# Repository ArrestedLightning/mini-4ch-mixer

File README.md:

# Mini 4 Channel Audio Mixer

A very simple active audio mixer with 4 3.5mm inputs, and 1 3.5mm output.  USB-powered.  The default gain is 1:1 on all channels, although this can be changed by altering resistor values and/or installing potentiometers.  I built this as a simple way to run multiple sources into a set of computer speakers.  It is designed to fit in a commonly-available 90x70x28mm enclosure with end panels that can be either laser-cut or made from PCBs.

This project uses symbols from https://github.com/ArrestedLightning/al_kicad_libraries/.  It is licensed CC BY 4.0.

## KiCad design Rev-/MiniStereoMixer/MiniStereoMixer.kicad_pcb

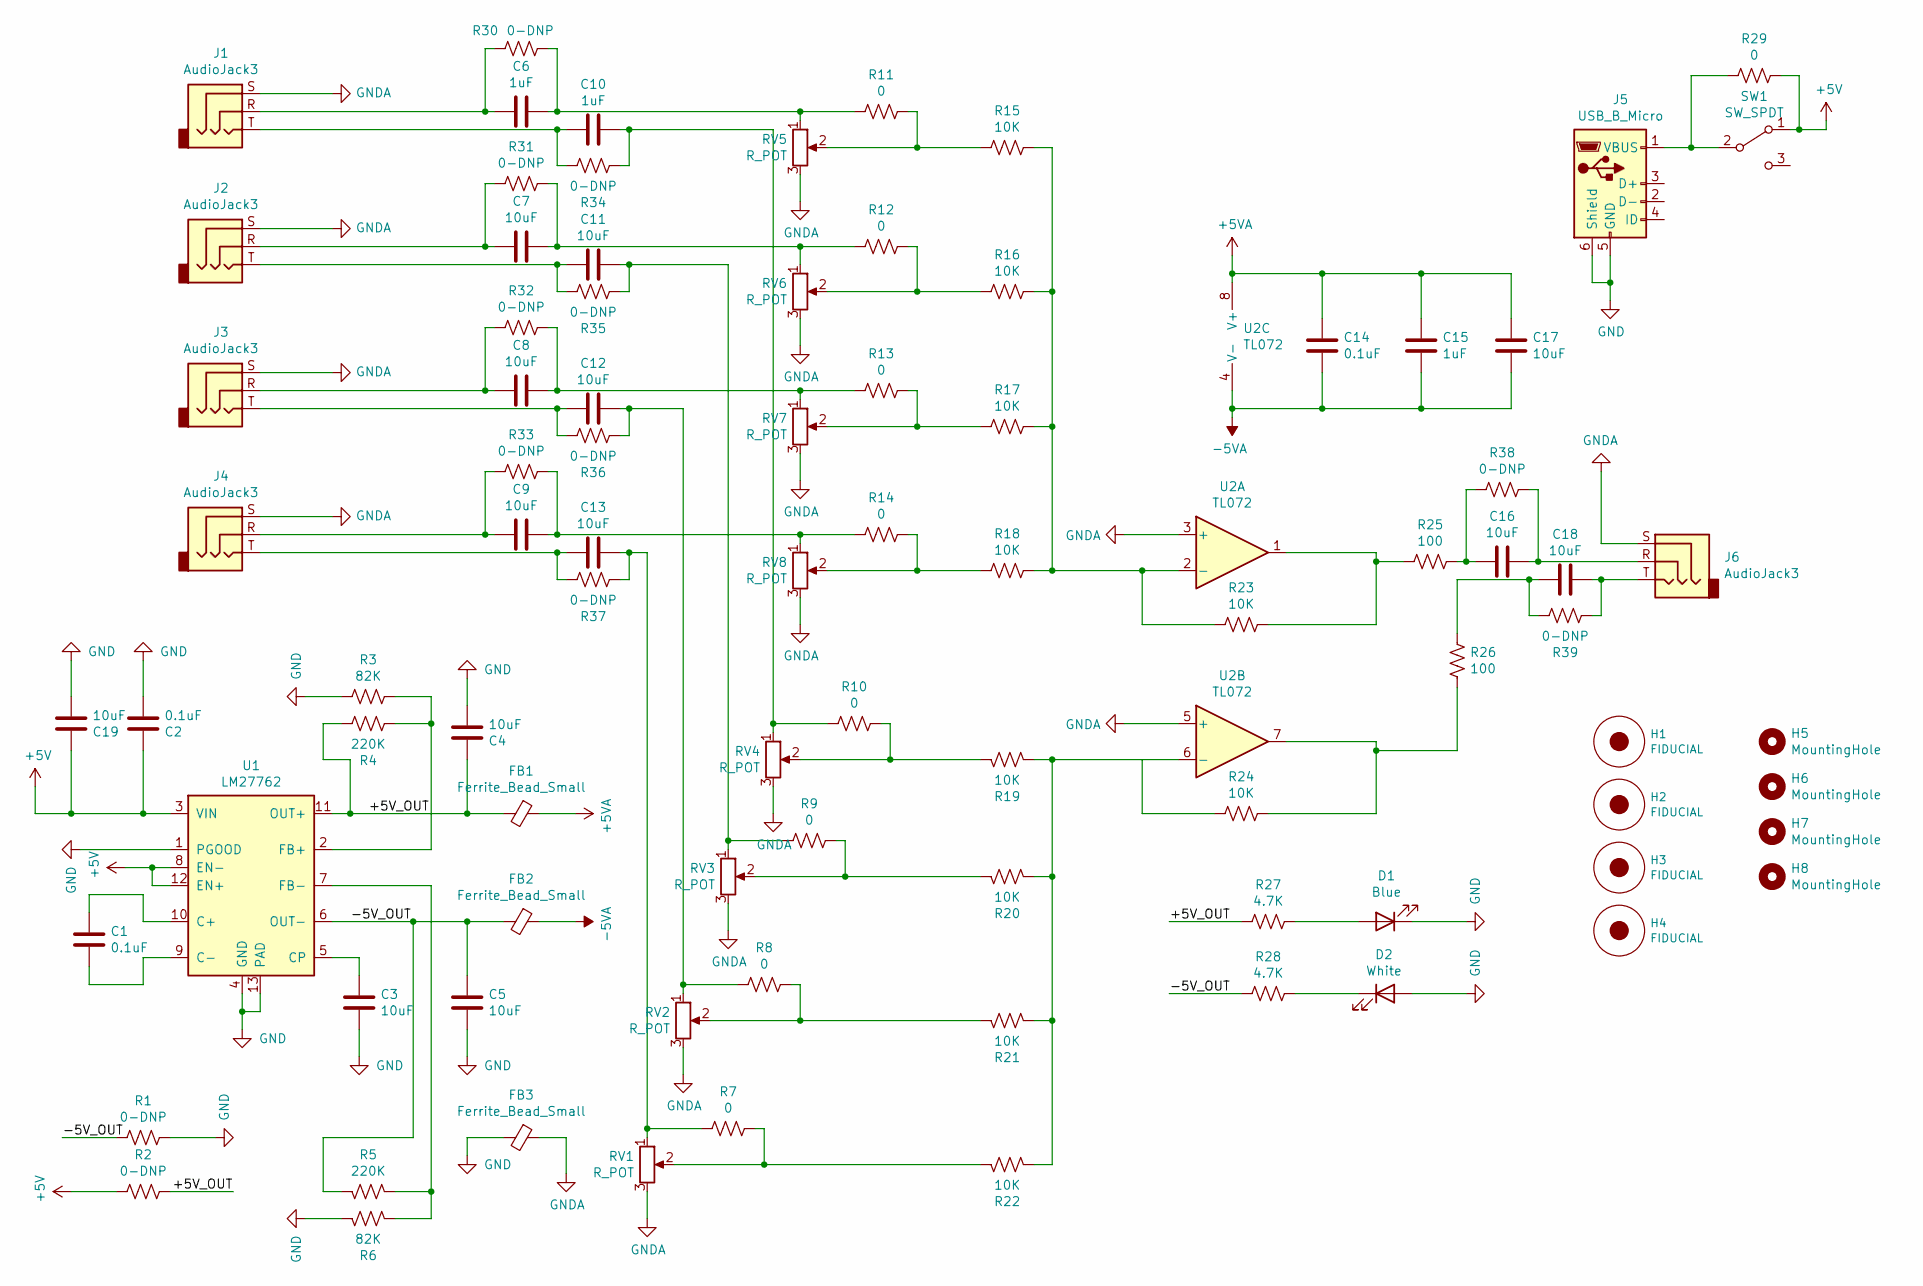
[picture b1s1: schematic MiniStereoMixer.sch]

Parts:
C1, C2, C14: 0.1uF; C_0805_2012Metric_Pad1.15x1.40mm_HandSolder; JLCPCB C49678
C3, C4, C5, C7, C8, C9, C11, C12, C13, C16, C17, C18, C19: 10uF; C_0805_2012Metric_Pad1.15x1.40mm_HandSolder; JLCPCB C15850
C6, C10, C15: 1uF; C_0805_2012Metric_Pad1.15x1.40mm_HandSolder; JLCPCB C28323
D1: Blue; LED_0805_2012Metric_Pad1.15x1.40mm_HandSolder; JLCPCB C2293
D2: White; LED_0805_2012Metric_Pad1.15x1.40mm_HandSolder; JLCPCB C34499
FB1, FB2, FB3: Ferrite_Bead_Small; R_0805_2012Metric_Pad1.15x1.40mm_HandSolder; JLCPCB C1017
H1, H2, H3, H4: FIDUCIAL; Fiducial_1.5mm_Mask3mm
H5, H6, H7, H8: MountingHole; MountingHole_3.2mm_M3_Pad
J1, J2, J3, J4, J6: AudioJack3; 3.5mmAudioJack
J5: USB_B_Micro; USB_Micro_A_SMD_HANDSOLDER_SMALLPADS
R1, R2, R30, R31, R32, R33, R34, R35, R36, R37, R38, R39: 0-DNP; R_0805_2012Metric_Pad1.15x1.40mm_HandSolder
R3, R6: 82K; R_0805_2012Metric_Pad1.15x1.40mm_HandSolder; JLCPCB C17840
R4, R5: 220K; R_0805_2012Metric_Pad1.15x1.40mm_HandSolder; JLCPCB C17556
R7, R8, R9, R10, R11, R12, R13, R14, R29: 0; R_0805_2012Metric_Pad1.15x1.40mm_HandSolder; JLCPCB C17477
R15, R16, R17, R18, R19, R20, R21, R22, R23, R24: 10K; R_0805_2012Metric_Pad1.15x1.40mm_HandSolder; JLCPCB C17414
R25, R26: 100; R_0805_2012Metric_Pad1.15x1.40mm_HandSolder; JLCPCB C17408
R27, R28: 4.7K; R_0805_2012Metric_Pad1.15x1.40mm_HandSolder; JLCPCB C17673
RV1, RV2, RV3, RV4, RV5, RV6, RV7, RV8: R_POT; potentiometer_3x5mm
SW1: SW_SPDT; PinHeader_1x03_P2.54mm_Horizontal
U1: LM27762; WSON-12-1EP_3x2mm_P0.5mm_EP1x2.65_ThermalVias; JLCPCB C134018
U2: TL072; SO-8_3.9x4.9mm_P1.27mm; JLCPCB C6961

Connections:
+5V: C2.1, C19.1, R2.2, R29.1, SW1.1 (A), U1.3 (VIN), U1.8 (EN-), U1.12 (EN+)
+5VA: C14.1, C15.1, C17.1, FB1.1, U2.8 (V+)
-5VA: C14.2, C15.2, C17.2, FB2.1, U2.4 (V-)
/+5V_OUT: C4.1, FB1.2, R2.1, R4.1, R27.2, U1.11 (OUT+)
/-5V_OUT: C5.1, FB2.2, R1.2, R5.1, R28.2, U1.6 (OUT-)
GND: C2.2, C3.2, C4.2, C5.2, C19.2, D1.1 (K), D2.2 (A), FB3.2, J5.5 (GND), J5.6 (Shield), R1.1, R3.2, R6.2, U1.1 (PGOOD), U1.4 (GND), U1.13 (PAD)
GNDA: FB3.1, J1.S, J2.S, J3.S, J4.S, J6.S, RV1.3, RV2.3, RV3.3, RV4.3, RV5.3, RV6.3, RV7.3, RV8.3, U2.3 (+), U2.5 (+)
unnamed: C1.1, U1.10 (C+)
unnamed: C1.2, U1.9 (C-)
unnamed: C3.1, U1.5 (CP)
unnamed: C6.1, R11.2, R30.1, RV5.1
unnamed: C6.2, J1.R, R30.2
unnamed: C7.1, R12.2, R31.1, RV6.1
unnamed: C7.2, J2.R, R31.2
unnamed: C8.1, R13.2, R32.1, RV7.1
unnamed: C8.2, J3.R, R32.2
unnamed: C9.1, R14.2, R33.1, RV8.1
unnamed: C9.2, J4.R, R33.2
unnamed: C10.1, R10.2, R34.2, RV4.1
unnamed: C10.2, J1.T, R34.1
unnamed: C11.1, R9.2, R35.2, RV3.1
unnamed: C11.2, J2.T, R35.1
unnamed: C12.1, R8.2, R36.2, RV2.1
unnamed: C12.2, J3.T, R36.1
unnamed: C13.1, R7.2, R37.2, RV1.1
unnamed: C13.2, J4.T, R37.1
unnamed: C16.1, J6.R, R38.1
unnamed: C16.2, R25.1, R38.2
unnamed: C18.1, J6.T, R39.2
unnamed: C18.2, R26.2, R39.1
unnamed: D1.2 (A), R27.1
unnamed: D2.1 (K), R28.1
unnamed: J5.1 (VBUS), R29.2, SW1.2 (B)
unnamed: R3.1, R4.2, U1.2 (FB+)
unnamed: R5.2, R6.1, U1.7 (FB-)
unnamed: R10.1, R19.2, RV4.2
unnamed: R11.1, R15.2, RV5.2
unnamed: R12.1, R16.2, RV6.2
unnamed: R13.1, R17.2, RV7.2
unnamed: R14.1, R18.2, RV8.2
unnamed: R15.1, R16.1, R17.1, R18.1, R23.2, U2.2 (-)
unnamed: R19.1, R20.1, R21.1, R22.1, R24.2, U2.6 (-)
unnamed: R9.1, R20.2, RV3.2
unnamed: R8.1, R21.2, RV2.2
unnamed: R7.1, R22.2, RV1.2
unnamed: R23.1, R25.2, U2.1
unnamed: R24.1, R26.1, U2.7

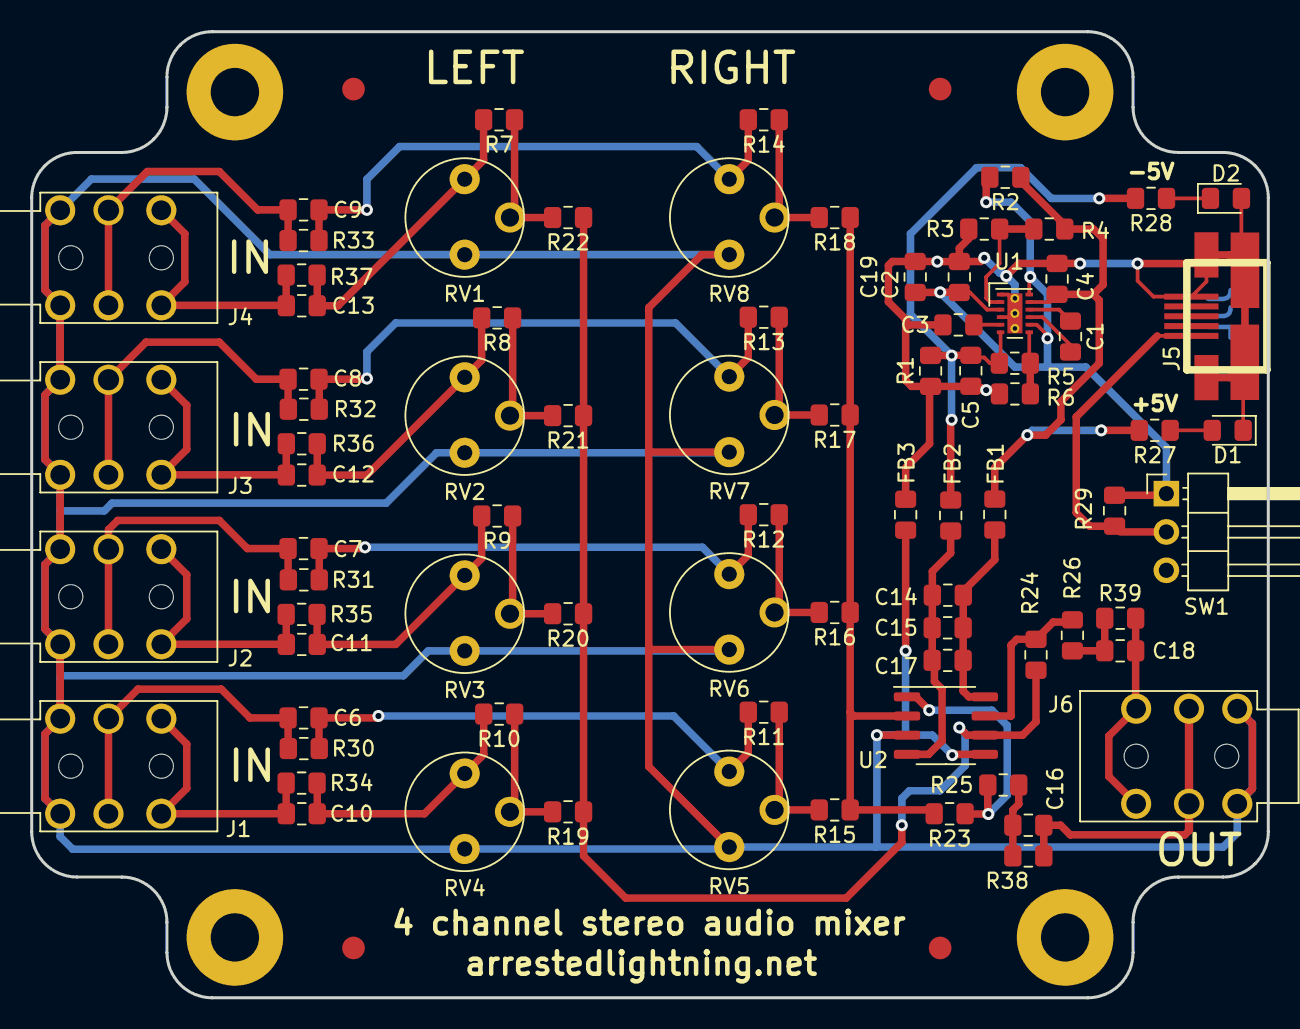
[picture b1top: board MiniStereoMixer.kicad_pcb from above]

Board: 2 copper layers, 81.9 x 64.0 mm, 88 parts (0 on the bottom side), 47 nets.

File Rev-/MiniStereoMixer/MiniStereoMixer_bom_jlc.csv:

"Comment","Designator","Footprint","LCSC Part #"
"0.1uF","C14,C1,C2","C_0805_2012Metric_Pad1.15x1.40mm_HandSolder","C49678"
"1uF","C15,C6,C10","C_0805_2012Metric_Pad1.15x1.40mm_HandSolder","C28323"
"10uF","C17,C16,C18,C7,C11,C8,C12,C9,C13,C3,C5,C4,C19","C_0805_2012Metric_Pad1.15x1.40mm_HandSolder","C15850"
"Blue","D1","LED_0805_2012Metric_Pad1.15x1.40mm_HandSolder","C2293"
"White","D2","LED_0805_2012Metric_Pad1.15x1.40mm_HandSolder","C34499"
"Ferrite_Bead_Small","FB1,FB2,FB3","R_0805_2012Metric_Pad1.15x1.40mm_HandSolder","C1017"
"82K","R3,R6","R_0805_2012Metric_Pad1.15x1.40mm_HandSolder","C17840"
"220K","R4,R5","R_0805_2012Metric_Pad1.15x1.40mm_HandSolder","C17556"
"0","R11,R13,R12,R14,R10,R9,R8,R7,R29","R_0805_2012Metric_Pad1.15x1.40mm_HandSolder","C17477"
"10K","R23,R24,R18,R17,R16,R15,R19,R20,R21,R22","R_0805_2012Metric_Pad1.15x1.40mm_HandSolder","C17414"
"100","R25,R26","R_0805_2012Metric_Pad1.15x1.40mm_HandSolder","C17408"
"4.7K","R27,R28","R_0805_2012Metric_Pad1.15x1.40mm_HandSolder","C17673"
"LM27762","U1","WSON-12-1EP_3x2mm_P0.5mm_EP1x2.65_ThermalVias","C134018"
"TL072","U2","SO-8_3.9x4.9mm_P1.27mm","C6961"

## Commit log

2021-02-06 Create LICENSE
2021-02-06 Initial Commit of design files
